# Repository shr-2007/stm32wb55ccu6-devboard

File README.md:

# STM32WB55CCU6 Development Board

**A custom four-layer STM32WB55CCU6 development-board design by Canal Star Tech.**

> **Project status:** V1.0 PCB design completed; fabrication pending.

## PCB Renders

### Front Side

### Back Side

## Schematic
[View the complete schematic PDF](Hardware/PDF/schematic.pdf)

This repository contains the independently recreated and developed hardware design for a custom development board based on the STMicroelectronics STM32WB55CCU6 wireless microcontroller.

The project explores schematic capture, component selection, USB-C interfacing, 3.3 V power regulation, clock circuitry, SWD programming access, UART connectivity, RF interfacing and four-layer PCB layout using KiCad.

The schematic and PCB were recreated independently. Phil's Lab's STM32 Bluetooth hardware-design tutorial was used as an educational reference; the component placement, PCB routing and board presentation in this repository are this project's own design work.

## Main features

- **MCU:** STM32WB55CCU6
- **USB:** USB Type-C receptacle
- **Power:** 5 V USB input and 3.3 V regulation
- **Regulator:** MIC5366-3.3YC5
- **Clock sources:** 32 MHz HSE and 32.768 kHz LSE
- **Debug/programming:** SWD interface and BOOT switch
- **Serial:** UART header
- **RF:** External RF connector footprint; dedicated PCB antenna planned for V2.0
- **EDA:** KiCad
- **PCB:** Four copper layers

## PCB stackup

| Layer | Assigned net/function |
|---|---|
| F.Cu | GND |
| In1.Cu | GND |
| In2.Cu | 3V3 |
| B.Cu | 3V3 |

This table records the current design intent. Confirm the final fabrication stackup and copper weights with the selected manufacturer before ordering.

## Repository contents

| Directory/file | Contents |
|---|---|
| `Hardware/KiCad/` | Native KiCad schematic, PCB and project files |
| `Hardware/PDF/` | Schematic and other exported PDFs |
| `Hardware/Gerber/` | Fabrication outputs, when generated |
| `Documentation/` | Design notes, BOM and validation records |
| `Images/` | PCB renders and project images |
| `LICENSE` | CERN-OHL-S-2.0 license text |
| `LICENSES/` | Third-party attribution notes |

## Design status and limitations

V1.0 is a PCB design prototype. The board has **not yet been manufactured or electrically validated**. In particular, power-up, USB operation, SWD programming, clock startup, RF performance and Bluetooth functionality remain to be tested on assembled hardware.

A dedicated PCB antenna implementation and associated RF validation are planned for V2.0. The V1.0 external RF connector/footprint should not be interpreted as proof of a validated RF path.

## Future work — V2.0

- Dedicated PCB antenna design and RF matching network.
- RF layout review, impedance planning and validation.
- PCB fabrication and assembly.
- Power-rail and current-consumption measurements.
- Clock startup and accuracy checks.
- USB and SWD bring-up.
- UART and GPIO verification.
- Bluetooth Low Energy testing.

## Acknowledgements

Phil's Lab's STM32 Bluetooth hardware-design tutorial was used as an educational reference:

https://youtu.be/PlXd3lLZ4vc

The schematic capture, component placement, PCB layout, routing and Canal Star Tech branding in this repository were independently recreated and developed for this project.

## License

The original hardware design files explicitly covered by this project are licensed under **CERN Open Hardware Licence Version 2 — Strongly Reciprocal (CERN-OHL-S-2.0)**. See [`LICENSE`](LICENSE) 

Third-party components, manufacturer documentation, trademarks and externally sourced library assets remain subject to their respective terms. See [`LICENSES/Third_Party_Attributions.md`](LICENSES/Third_Party_Attributions.md).

**SPDX-License-Identifier:** `CERN-OHL-S-2.0`

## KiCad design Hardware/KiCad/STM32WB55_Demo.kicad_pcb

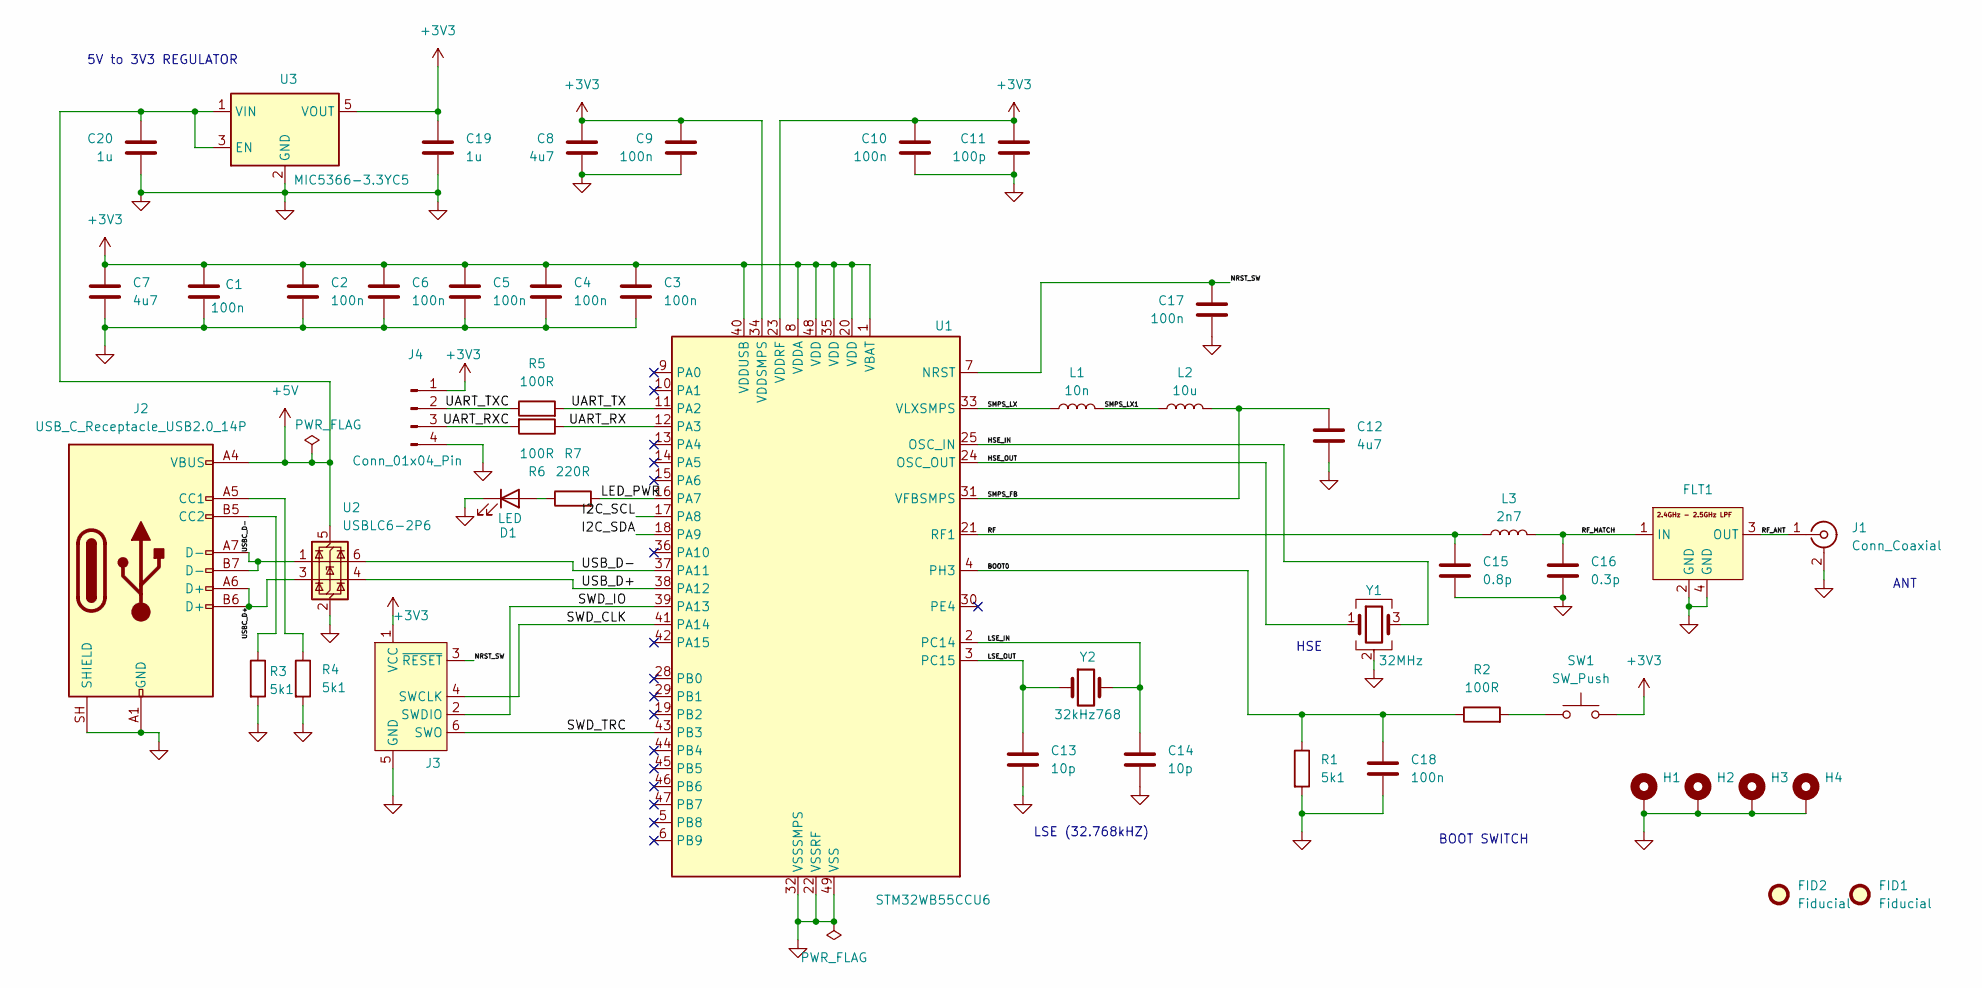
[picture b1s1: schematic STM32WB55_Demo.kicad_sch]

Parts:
C1, C2, C3, C4, C5, C6, C9, C10, C17, C18: 100n; C_0603_1608Metric
C7, C8, C12: 4u7; C_0603_1608Metric
C11: 100p; C_0402_1005Metric
C13, C14: 10p; C_0402_1005Metric
C15: 0.8p; C_0402_1005Metric
C16: 0.3p; C_0402_1005Metric
C19, C20: 1u; C_0603_1608Metric
D1: LED; LED_0805_2012Metric
FID1, FID2: Fiducial; Fiducial_0.5mm_Mask1.5mm
FLT1: DLF162500LT-5028A1
H1, H2, H3, H4: MountingHole_Pad; MountingHole_2.2mm_M2_Pad_Via
J1: Conn_Coaxial; MMCX_Molex_73415-1471_Vertical
J2: USB_C_Receptacle_USB2.0_14P; USB_C_Receptacle_GCT_USB4105-xx-A_16P_TopMnt_Horizontal
J3: Conn_ARM_SWD_TagConnect_TC2030; Tag-Connect_TC2030-IDC-FP_2x03_P1.27mm_Vertical
J4: Conn_01x04_Pin; Molex_PicoBlade_53048-0410_1x04_P1.25mm_Horizontal
L1: 10n; L_0402_1005Metric
L2: 10u; L_0805_2012Metric
L3: 2n7; L_0402_1005Metric
R1, R3, R4: 5k1; R_0805_2012Metric
R2, R5, R6: 100R; R_0805_2012Metric
R7: 220R; R_0805_2012Metric
SW1: SW_Push; SW_Push_SPST_NO_Alps_SKRK
U1: STM32WB55CCU6; QFN-48-1EP_7x7mm_P0.5mm_EP5.6x5.6mm
U2: USBLC6-2P6; SOT-666
U3: MIC5366-3.3YC5; SOT-353_SC-70-5
Y1: 32MHz; Crystal_SMD_2016-4Pin_2.0x1.6mm
Y2: 32kHz768; Crystal_SMD_2012-2Pin_2.0x1.2mm

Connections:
+3V3: C1.1, C2.1, C3.1, C4.1, C5.1, C6.1, C7.1, C8.1, C9.1, C10.1, C11.1, C19.1, J3.1 (VCC), J4.1, SW1.2, U1.1 (VBAT), U1.8 (VDDA), U1.20 (VDD), U1.23 (VDDRF), U1.34 (VDDSMPS), U1.35 (VDD), U1.40 (VDDUSB), U1.48 (VDD), U3.5 (VOUT)
+5V: C20.1, J2.A4 (VBUS), J2.A9 (VBUS), J2.B4 (VBUS), J2.B9 (VBUS), U2.5 (VBUS), U3.1 (VIN), U3.3 (EN)
/BOOT0: C18.1, R1.1, R2.1, U1.4 (PH3)
/HSE_IN: U1.25 (OSC_IN), Y1.3
/HSE_OUT: U1.24 (OSC_OUT), Y1.1
/I2C_SCL: U1.17 (PA8)
/I2C_SDA: U1.18 (PA9)
/LED_PWR: R7.2, U1.16 (PA7)
/LSE_IN: C14.1, U1.2 (PC14), Y2.2
/LSE_OUT: C13.1, U1.3 (PC15), Y2.1
/NRST_SW: C17.1, J3.3 (~RESET), U1.7 (NRST)
/RF: C15.1, L3.1, U1.21 (RF1)
/RF_ANT: FLT1.3 (OUT), J1.1 (In)
/RF_MATCH: C16.1, FLT1.1 (IN), L3.2
/SMPS_FB: C12.1, L2.2, U1.31 (VFBSMPS)
/SMPS_LX: L1.1, U1.33 (VLXSMPS)
/SMPS_LX1: L1.2, L2.1
/SWD_CLK: J3.4 (SWCLK), U1.41 (PA14)
/SWD_IO: J3.2 (SWDIO), U1.39 (PA13)
/SWD_TRC: J3.6 (SWO), U1.43 (PB3)
/UART_RX: R6.1, U1.12 (PA3)
/UART_RXC: J4.3, R6.2
/UART_TX: R5.2, U1.11 (PA2)
/UART_TXC: J4.2, R5.1
/USBC_D+: J2.A6 (D+), J2.B6 (D+), U2.3 (I/O2)
/USBC_D-: J2.A7 (D-), J2.B7 (D-), U2.1 (I/O1)
/USB_D+: U1.38 (PA12), U2.4 (I/O2)
/USB_D-: U1.37 (PA11), U2.6 (I/O1)
GND: C1.2, C2.2, C3.2, C4.2, C5.2, C6.2, C7.2, C8.2, C9.2, C10.2, C11.2, C12.2, C13.2, C14.2, C15.2, C16.2, C17.2, C18.2, C19.2, C20.2, D1.1 (K), FLT1.2 (GND), FLT1.4 (GND), H1.1 (1_1), H2.1 (1_1), H3.1 (1_1), H4.1 (1_1), J1.2 (Ext), J2.A1 (GND), J2.A12 (GND), J2.B1 (GND), J2.B12 (GND), J2.SH (SHIELD), J3.5 (GND), J4.4, R1.2, R3.2, R4.2, U1.22 (VSSRF), U1.32 (VSSSMPS), U1.49 (VSS), U2.2 (GND), U3.2 (GND), Y1.2 (G), Y1.4 (G)
unnamed: D1.2 (A), R7.1
unnamed: J2.A5 (CC1), R4.1
unnamed: J2.B5 (CC2), R3.1
unnamed: R2.2, SW1.1

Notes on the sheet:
BOOT SWITCH
LSE (32.768kHZ)
HSE
5V to 3V3 REGULATOR
ANT

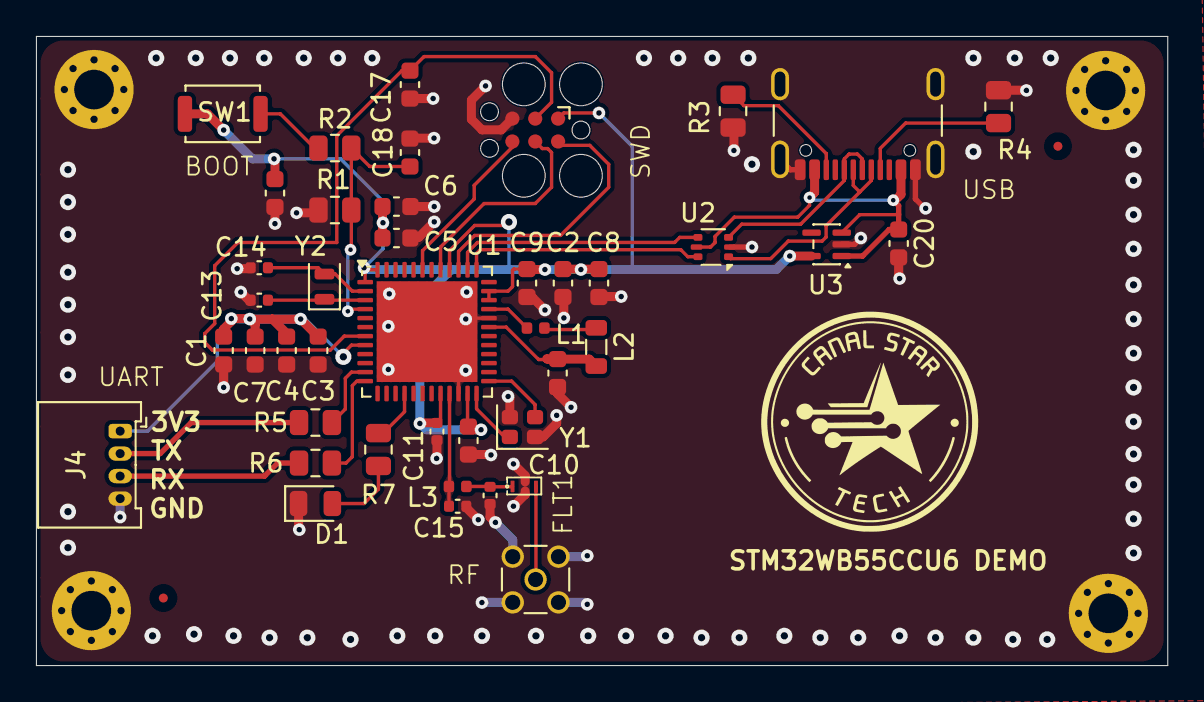
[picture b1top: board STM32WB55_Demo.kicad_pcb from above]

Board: 4 copper layers, 62.8 x 35.0 mm, 48 parts (0 on the bottom side), 31 nets.

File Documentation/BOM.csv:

"Reference","Qty","Value","DNP","Exclude from BOM","Exclude from Board","Exclude from Simulation","Exclude from Position Files","Footprint","Datasheet"
"C1,C2,C3,C4,C5,C6,C9,C10,C17,C18","10","100n","","","","","${EXCLUDE_FROM_POS_FILES}","Capacitor_SMD:C_0603_1608Metric",""
"C7,C8,C12","3","4u7","","","","","${EXCLUDE_FROM_POS_FILES}","Capacitor_SMD:C_0603_1608Metric",""
"C11","1","100p","","","","","${EXCLUDE_FROM_POS_FILES}","Capacitor_SMD:C_0402_1005Metric",""
"C13,C14","2","10p","","","","","${EXCLUDE_FROM_POS_FILES}","Capacitor_SMD:C_0402_1005Metric",""
"C15","1","0.8p","","","","","${EXCLUDE_FROM_POS_FILES}","Capacitor_SMD:C_0402_1005Metric",""
"C16","1","0.3p","","","","","${EXCLUDE_FROM_POS_FILES}","Capacitor_SMD:C_0402_1005Metric",""
"C19,C20","2","1u","","","","","${EXCLUDE_FROM_POS_FILES}","Capacitor_SMD:C_0603_1608Metric",""
"D1","1","LED","","","","","${EXCLUDE_FROM_POS_FILES}","LED_SMD:LED_0805_2012Metric",""
"FLT1","1","","","","","","${EXCLUDE_FROM_POS_FILES}","STM32WB55_Footprints:DLF162500LT-5028A1",""
"J1","1","Conn_Coaxial","","","","","${EXCLUDE_FROM_POS_FILES}","Connector_Coaxial:MMCX_Molex_73415-1471_Vertical",""
"J2","1","USB_C_Receptacle_USB2.0_14P","","","","","${EXCLUDE_FROM_POS_FILES}","Connector_USB:USB_C_Receptacle_GCT_USB4105-xx-A_16P_TopMnt_Horizontal","https://www.usb.org/sites/default/files/documents/usb_type-c.zip"
"J4","1","Conn_01x04_Pin","","","","","${EXCLUDE_FROM_POS_FILES}","Connector_Molex:Molex_PicoBlade_53048-0410_1x04_P1.25mm_Horizontal",""
"L1","1","10n","","","","","${EXCLUDE_FROM_POS_FILES}","Inductor_SMD:L_0402_1005Metric",""
"L2","1","10u","","","","","${EXCLUDE_FROM_POS_FILES}","Inductor_SMD:L_0805_2012Metric",""
"L3","1","2n7","","","","","${EXCLUDE_FROM_POS_FILES}","Inductor_SMD:L_0402_1005Metric",""
"R1,R3,R4","3","5k1","","","","","${EXCLUDE_FROM_POS_FILES}","Resistor_SMD:R_0805_2012Metric",""
"R2,R5,R6","3","100R","","","","","${EXCLUDE_FROM_POS_FILES}","Resistor_SMD:R_0805_2012Metric",""
"R7","1","220R","","","","","${EXCLUDE_FROM_POS_FILES}","Resistor_SMD:R_0805_2012Metric",""
"SW1","1","SW_Push","","","","","${EXCLUDE_FROM_POS_FILES}","Button_Switch_SMD:SW_Push_SPST_NO_Alps_SKRK",""
"U1","1","STM32WB55CCU6","","","","","${EXCLUDE_FROM_POS_FILES}","Package_DFN_QFN:QFN-48-1EP_7x7mm_P0.5mm_EP5.6x5.6mm","https://www.st.com/resource/en/datasheet/stm32wb55cc.pdf"
"U2","1","USBLC6-2P6","","","","","${EXCLUDE_FROM_POS_FILES}","Package_TO_SOT_SMD:SOT-666","https://www.st.com/resource/en/datasheet/usblc6-2.pdf"
"U3","1","MIC5366-3.3YC5","","","","","${EXCLUDE_FROM_POS_FILES}","Package_TO_SOT_SMD:SOT-353_SC-70-5","https://ww1.microchip.com/downloads/aemDocuments/documents/A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"
"Y1","1","32MHz","","","","","${EXCLUDE_FROM_POS_FILES}","Crystal:Crystal_SMD_2016-4Pin_2.0x1.6mm",""
"Y2","1","32kHz768","","","","","${EXCLUDE_FROM_POS_FILES}","Crystal:Crystal_SMD_2012-2Pin_2.0x1.2mm",""
